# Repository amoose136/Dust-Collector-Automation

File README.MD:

A project to make a few pcbs that control our cyclone dust collector in the wood shop in reponse to tool usage and whether or not the dust bin is full. Operates of Lora radio.

WIP

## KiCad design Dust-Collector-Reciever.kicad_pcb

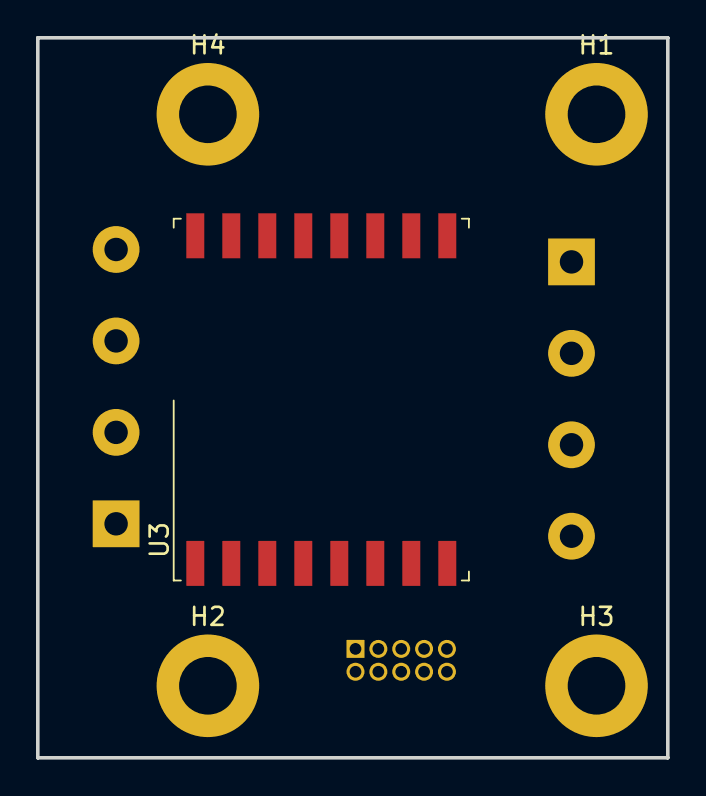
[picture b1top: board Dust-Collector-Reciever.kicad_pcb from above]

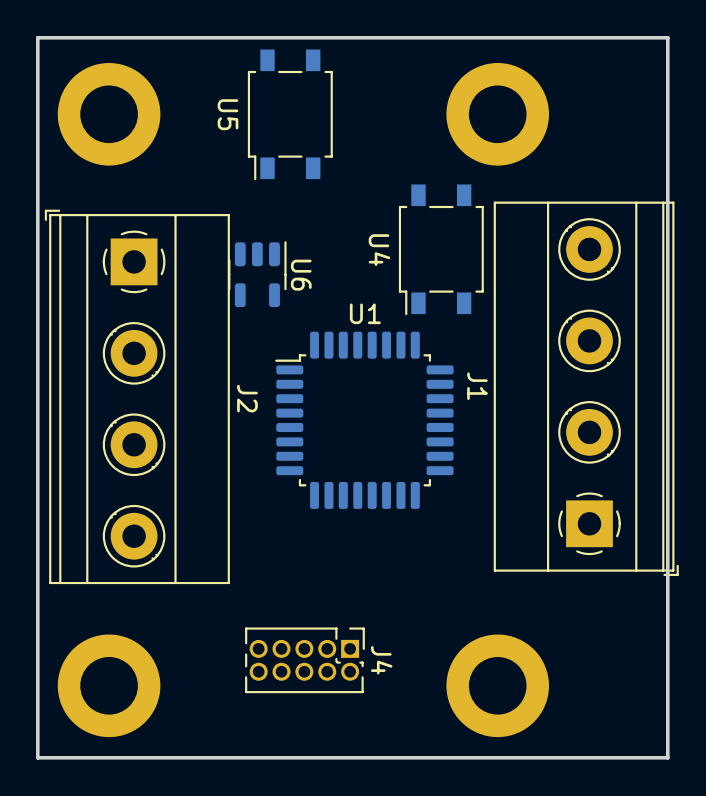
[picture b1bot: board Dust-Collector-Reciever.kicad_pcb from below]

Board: 2 copper layers, 35.0 x 40.0 mm, 12 parts (7 on the bottom side), 9 nets, no tracks yet.

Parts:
H1, H2, H3, H4: MountingHole; MountingHole_3.2mm_M3_ISO7380_Pad
J1, J2: Screw_Terminal_01x04; TerminalBlock_Phoenix_MKDS-1,5-4-5.08_1x04_P5.08mm_Horizont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
J4: Conn_ARM_JTAG_SWD_10; PinHeader_2x05_P1.27mm_Vertical
U1: STM32L010K4T6-ND; LQFP-32_7x7mm_P0.8mm
U3: RFM69HCW; HOPERF_RFM69HW
U4: CPC1006N NO; SO-4_4.4x4.3mm_P2.54mm
U5: CPC1106N NC; SO-4_4.4x4.3mm_P2.54mm
U6: AP2112K-3.3; SOT-23-5

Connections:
/3v3in: J2.1, U6.1 (VIN)
/NC/ON Switch IN: J1.3, U5.4
/NC/ON Switch OUT: J1.2, U5.3
/NO/OFF Switch IN: J2.4, U4.4
/NO/OFF Switch Switch OUT: J2.3, U4.3
GND: J2.2, U4.2, U5.2, U6.2 (GND)
unnamed: J4.3 (GND), J4.5 (GND)
unnamed: U1.14 (PB0), U5.1
unnamed: U1.15 (PB1), U4.1

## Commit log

2023-06-17 WIP - around 70% done on schematic
2023-06-17 cleanup project, add images to readme
